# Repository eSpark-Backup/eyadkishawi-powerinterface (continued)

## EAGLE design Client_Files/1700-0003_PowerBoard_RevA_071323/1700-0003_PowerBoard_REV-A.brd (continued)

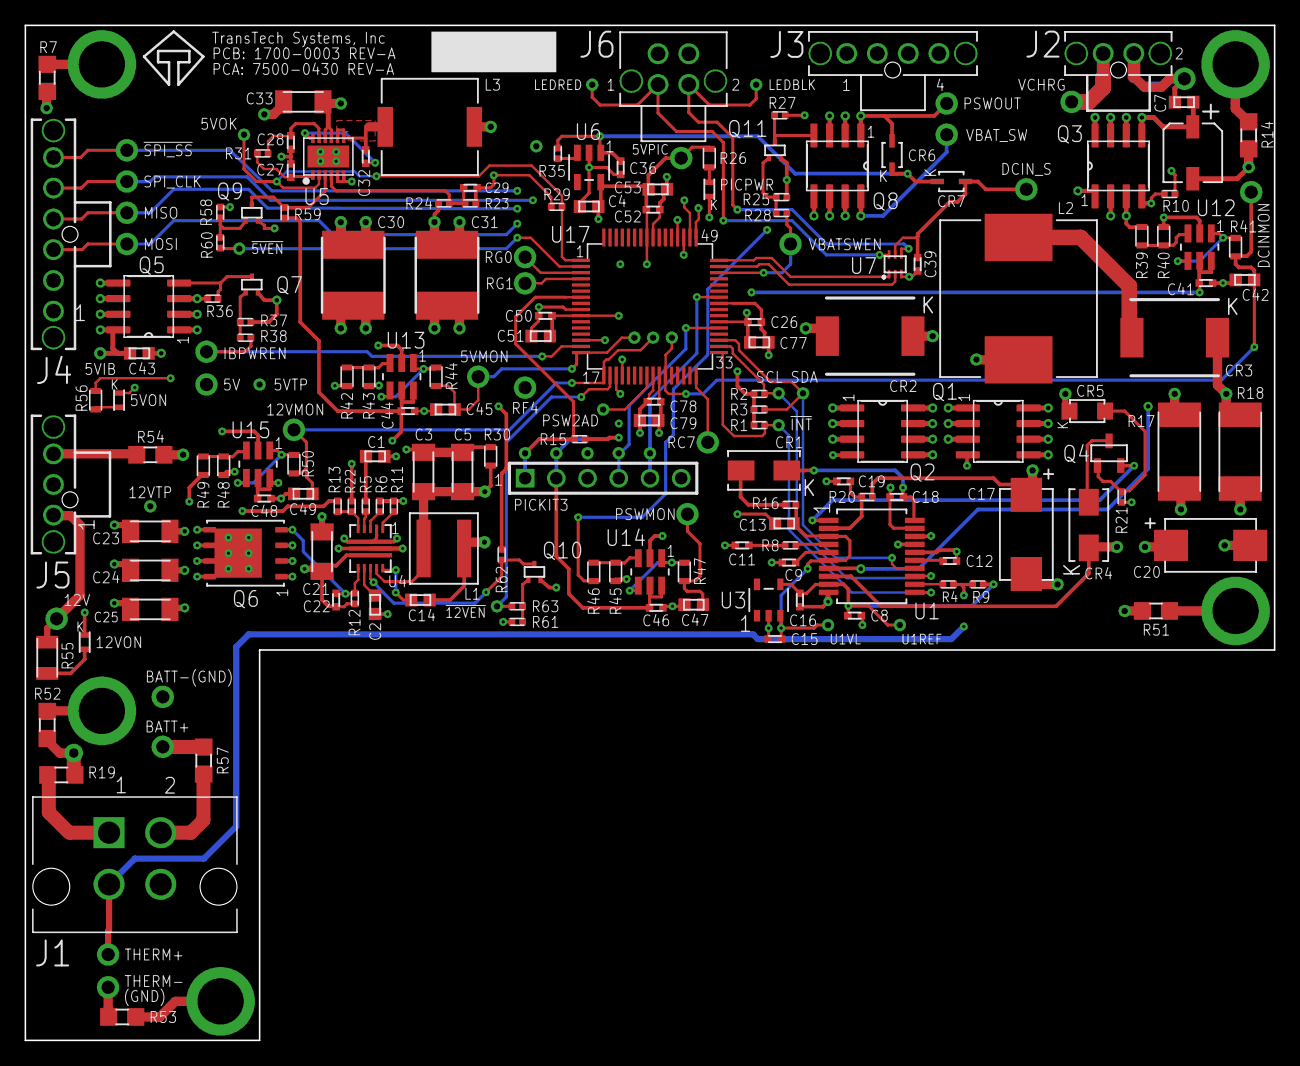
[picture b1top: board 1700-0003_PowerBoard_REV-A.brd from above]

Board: 4 copper layers, 101.6 x 82.5 mm, 205 parts (0 on the bottom side), 100 nets.

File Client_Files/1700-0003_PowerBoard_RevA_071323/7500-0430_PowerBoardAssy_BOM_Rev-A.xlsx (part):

PART | VALUE | DEVICE | PACKAGE | DESCRIPTION | COPYRIGHT | MANUFACTURER | MANUFACTURER_PART_NUMBER | PACKAGE | PART_DESC | QTY_AREA
U4 | REGULATOR_BOOST_TI_TPS61178RNWT | REGULATOR_BOOST_TI_TPS61178RNWT | RNW0013A |  | Copyright (C) 2022 Ultra Librarian. All rights reserved. | TI | TPS61178RNWT |  | IC REG BOOST ADJ 10A 13VQFN
Q1 | N-CH/30V/11A/8-SOIC | MOSFET_N-CH_DIODES-INC_DMS3015SSS-13 | SOIC127P600X175-8N | ENHANCEMENT MODE MOSFET |  | DIODES INC. | DMS3015SSS-13 |  | N-Channel 30 V 11A (Ta) 1.55W (Ta) Surface Mount 8-SO
Q2 | N-CH/30V/11A/8-SOIC | MOSFET_N-CH_DIODES-INC_DMS3015SSS-13 | SOIC127P600X175-8N | ENHANCEMENT MODE MOSFET |  | DIODES INC. | DMS3015SSS-13 |  | N-Channel 30 V 11A (Ta) 1.55W (Ta) Surface Mount 8-SO
C27 | DNP (0402) | CAP_CER_0402_MURATA | G-155_MUR |  |  | MURATA |  |  | --- DO NOT POPULATE ---
U7 | IC_H-BRIDGE_TI_DRV8220DRLR | IC_H-BRIDGE_TI_DRV8220DRLR | SOT5X3-6_DRL_TEX |  |  | TI | DRV8220DRLR |  | 20-V, 1-A H-BRIDGE MOTOR DRIVER
C30 | 47/50V (MLCC-SMD) | CAP_CER_TDK_CKG57 | CAP_CKG57N_TDK |  | Copyright (C) 2022 Ultra Librarian. All rights reserved. | TDK | CKG57NX7R1H476M500JH |  | 47 µF ±20% 50V Ceramic Capacitor X7R Stacked SMD, 2 J-Lead | (2X)
C31 | 47/50V | CAP_CER_TDK_CKG57 | CAP_CKG57N_TDK |  | Copyright (C) 2022 Ultra Librarian. All rights reserved. | TDK | CKG57NX7R1H476M500JH | (SMD-MLCC) | 47 µF ±20% 50V Ceramic Capacitor X7R Stacked SMD, 2 J-Lead | (2X)
Q4 | 45V/0.8A/SOT23 | TRANS_PNP_SOT-23-3_DIOTEC | SOT-23-3_DIOTEC |  |  | DIOTEC | BC807-40 |  | Bipolar Transistors - BJT Bipolar Transistor, SOT-23, 45V, 800mA, PNP
U5 | REGULATOR_BUCK_RENESAS_ISL85005AFRZ-T7A | REGULATOR_BUCK_RENESAS_ISL85005AFRZ-T7A | SON50P300X400X90-13N | RENESAS - ISL85005AFRZ-T7A - DC/DC CONV, SYNC BUCK, DFN-12 |  | RENESAS (INTERSIL) | ISL85005AFRZ-T7A |  | Buck Switching Regulator IC Positive Adjustable 5V 1 Output 5A 12-VFDFN Exposed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
C6 | 45224 | CAP_SMT_EL_CORNELL-DUB_AFK106M25B12T-FCAP_AFK106M25B12T-F_CND-L | CAP_AFK106M25B12T-F_CND-L |  | Copyright (C) 2023 Ultra Librarian. All rights reserved. | Cornell Dubilier | AFK106M25B12T-F |  | CAP ALUM 10UF 20% 25V SMD
C8 | 0.1 (0402) | CAP_CER_0402_MURATA | G-155_MUR |  |  | MURATA | GCM155R71C104KA55D |  | CAP CER 0.1UF 16V X7R 0402
C11 | 0.1 (0402) | CAP_CER_0402_MURATA | G-155_MUR |  |  | MURATA | GCM155R71C104KA55D |  | CAP CER 0.1UF 16V X7R 0402
C15 | 0.1 (0402) | CAP_CER_0402_MURATA | G-155_MUR |  |  | MURATA | GCM155R71C104KA55D |  | CAP CER 0.1UF 16V X7R 0402
C16 | 0.1 (0402) | CAP_CER_0402_MURATA | G-155_MUR |  |  | MURATA | GCM155R71C104KA55D |  | CAP CER 0.1UF 16V X7R 0402
C18 | 0.1 (0402) | CAP_CER_0402_MURATA | G-155_MUR |  |  | MURATA | GCM155R71C104KA55D |  | CAP CER 0.1UF 16V X7R 0402
C19 | 0.1 (0402) | CAP_CER_0402_MURATA | G-155_MUR |  |  | MURATA | GCM155R71C104KA55D |  | CAP CER 0.1UF 16V X7R 0402
C26 | 0.1/16V (0402) | CAP_CER_0402_MURATA | G-155_MUR |  |  | MURATA | GCM155R71C104KA55D |  | CAP CER 0.1UF 16V X7R 0402
C32 | 0.1 (0402) | CAP_CER_0402_MURATA | G-155_MUR |  |  | MURATA | GCM155R71C104KA55D |  | CAP CER 0.1UF 16V X7R 0402
C39 | 0.1 (0402) | CAP_CER_0402_MURATA | G-155_MUR |  |  | MURATA | GCM155R71C104KA55D |  | CAP CER 0.1UF 16V X7R 0402
C41 | 0.1 (0402) | CAP_CER_0402_MURATA | G-155_MUR |  |  | MURATA | GCM155R71C104KA55D |  | CAP CER 0.1UF 16V X7R 0402
C44 | 0.1 (0402) | CAP_CER_0402_MURATA | G-155_MUR |  |  | MURATA | GCM155R71C104KA55D |  | CAP CER 0.1UF 16V X7R 0402
C46 | 0.1 (0402) | CAP_CER_0402_MURATA | G-155_MUR |  |  | MURATA | GCM155R71C104KA55D |  | CAP CER 0.1UF 16V X7R 0402
C48 | 0.1 (0402) | CAP_CER_0402_MURATA | G-155_MUR |  |  | MURATA | GCM155R71C104KA55D |  | CAP CER 0.1UF 16V X7R 0402
C50 | 0.1/16V (0402) | CAP_CER_0402_MURATA | G-155_MUR |  |  | MURATA | GCM155R71C104KA55D |  | CAP CER 0.1UF 16V X7R 0402
C52 | 0.1/16V (0402) | CAP_CER_0402_MURATA | G-155_MUR |  |  | MURATA | GCM155R71C104KA55D |  | CAP CER 0.1UF 16V X7R 0402
C78 | 0.1/16V (0402) | CAP_CER_0402_MURATA | G-155_MUR |  |  | MURATA | GCM155R71C104KA55D |  | CAP CER 0.1UF 16V X7R 0402
C42 | 0.1/25V (0603) | CAP_CER_0603_TDK | CAP_C1608_TDK |  |  | KEMET | C0603C104K3RAC7867 |  | CAP CER 0.1UF 25V X7R 0603
C45 | 0.1/25V (0603) | CAP_CER_0603_TDK | CAP_C1608_TDK |  |  | KEMET | C0603C104K3RAC7867 |  | CAP CER 0.1UF 25V X7R 0603
C47 | 0.1/25V (0603) | CAP_CER_0603_TDK | CAP_C1608_TDK |  |  | KEMET | C0603C104K3RAC7867 |  | CAP CER 0.1UF 25V X7R 0603
C49 | 0.1/25V (0603) | CAP_CER_0603_TDK | CAP_C1608_TDK |  |  | KEMET | C0603C104K3RAC7867 |  | CAP CER 0.1UF 25V X7R 0603
C7 | 0.1/50V | CAP_CER_0603_TDK | CAP_C1608_TDK |  |  | SAMSUNG | CL10B104KB8NNNC | -603 | CAP CER 0.1UF 50V X7R 0603
C14 | 0.1/50V | CAP_CER_0603_TDK | CAP_C1608_TDK |  |  | SAMSUNG | CL10B104KB8NNNC | -603 | CAP CER 0.1UF 50V X7R 0603
C12 | 22nF (0402) | CAP_CER_0402_MURATA | G-155_MUR |  |  | MURATA | C0402C223K5REC7411 |  | CAP CER 0402 22NF 50V X7R 10%
C9 | 47nF (0402) | CAP_CER_0402_MURATA | G-155_MUR |  |  | MURATA | C0402C473K3REC7867 |  | CAP CER 0402 47NF 25V X7R 10%
C43 | 10/10V (0603) | CAP_CER_0603_TDK | CAP_C1608_TDK |  |  | MURATA | GRM188D71A106KA73D |  | CAP CER 10UF 10V X7T 0603
C51 | 10/10V (0603) | CAP_CER_0603_TDK | CAP_C1608_TDK |  |  | MURATA | GRM188D71A106KA73D |  | CAP CER 10UF 10V X7T 0603
C53 | 10/10V (0603) | CAP_CER_0603_TDK | CAP_C1608_TDK |  |  | MURATA | GRM188D71A106KA73D |  | CAP CER 10UF 10V X7T 0603
C77 | 10/10V (0603) | CAP_CER_0603_TDK | CAP_C1608_TDK |  |  | MURATA | GRM188D71A106KA73D |  | CAP CER 10UF 10V X7T 0603
C79 | 10/10V (0603) | CAP_CER_0603_TDK | CAP_C1608_TDK |  |  | MURATA | GRM188D71A106KA73D |  | CAP CER 10UF 10V X7T 0603
C21 | 10/50V (1206) | CAP_CER_1206_SAMSUNG | CAP_CL31_SAM |  | Copyright (C) 2022 Ultra Librarian. All rights reserved. | SAMSUNG | CL31B106KBHNNNE |  | CAP CER 10UF 50V X7R 1206 | (__X)
C29 | 12pF (0402) | CAP_CER_0402_MURATA | G-155_MUR |  |  | MURATA | C0402C120K5RAC7867 |  | CAP CER 12PF 50V X7R 0402
C28 | 1/25V (0402) | CAP_CER_0402_MURATA | G-155_MUR |  |  | MURATA | GRM155R61E105KA12D |  | CAP CER 1UF 25V X5R 0402
C13 | 1/25V | CAP_CER_0603_TDK | CAP_C1608_TDK |  |  | SAMSUNG | CL10B105KA8NNNC | -603 | CAP CER 1UF 25V X7R 0603
C36 | 1/10V (0402) | CAP_CER_0402_MURATA | G-155_MUR |  |  | MURATA | GRM155C81C225ME15D |  | CAP CER 2.2UF 16V X6S 0402
C1 | 220pF (0603) | CAP_CER_0603_TDK | CAP_C1608_TDK |  |  | SAMSUNG | CL10C221JB8NNNC |  | CAP CER 220PF 50V C0G/NP0 0603
C3 | 22/25V (1206) | CAP_CER_1206_SAMSUNG | CAP_CL31_SAM |  | Copyright (C) 2022 Ultra Librarian. All rights reserved. | SAMSUNG | CL31A226KAHNNNE |  | CAP CER 22UF 25V X5R 1206
C5 | 22/25V (1206) | CAP_CER_1206_SAMSUNG | CAP_CL31_SAM |  | Copyright (C) 2022 Ultra Librarian. All rights reserved. | SAMSUNG | CL31A226KAHNNNE |  | CAP CER 22UF 25V X5R 1206 | (2X)
C33 | 22/25V (1206) | CAP_CER_1206_SAMSUNG | CAP_CL31_SAM |  | Copyright (C) 2022 Ultra Librarian. All rights reserved. | SAMSUNG | CL31A226KAHNNNE |  | CAP CER 22UF 25V X5R 1206 | (2X)
C23 | 22/25V (1206) | CAP_CER_1206_SAMSUNG | CAP_CL31_SAM |  | Copyright (C) 2022 Ultra Librarian. All rights reserved. | SAMSUNG | GCM31CC81E226KE11L |  | CAP CER 22UF 25V X6S 1206 | (3X)
C24 | 22/25V (1206) | CAP_CER_1206_SAMSUNG | CAP_CL31_SAM |  | Copyright (C) 2022 Ultra Librarian. All rights reserved. | SAMSUNG | GCM31CC81E226KE11L |  | CAP CER 22UF 25V X6S 1206 | (3X)
C25 | 22/25V (1206) | CAP_CER_1206_SAMSUNG | CAP_CL31_SAM |  | Copyright (C) 2022 Ultra Librarian. All rights reserved. | SAMSUNG | GCM31CC81E226KE11L |  | CAP CER 22UF 25V X6S 1206 | (3X)
C2 | 4.7/16V (0603) | CAP_CER_0603_TDK | CAP_C1608_TDK |  |  | MURATA | GRM188Z71C475KE21D |  | CAP CER 4.7UF 16V X7R 0603
C4 | 4.7/16V (0603) | CAP_CER_0603_TDK | CAP_C1608_TDK |  |  | MURATA | GRM188Z71C475KE21D |  | CAP CER 4.7UF 16V X7R 0603
C17 | 22/35 (2917) | CAP_TANT_KEMET_2917 | CAPMP7.6X4.3_3.1N_KEM |  | Copyright (C) 2022 Ultra Librarian. All rights reserved. | KEMET | T495D226K035ATE300 |  | CAP TANT 22UF 10% 35V 2917
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
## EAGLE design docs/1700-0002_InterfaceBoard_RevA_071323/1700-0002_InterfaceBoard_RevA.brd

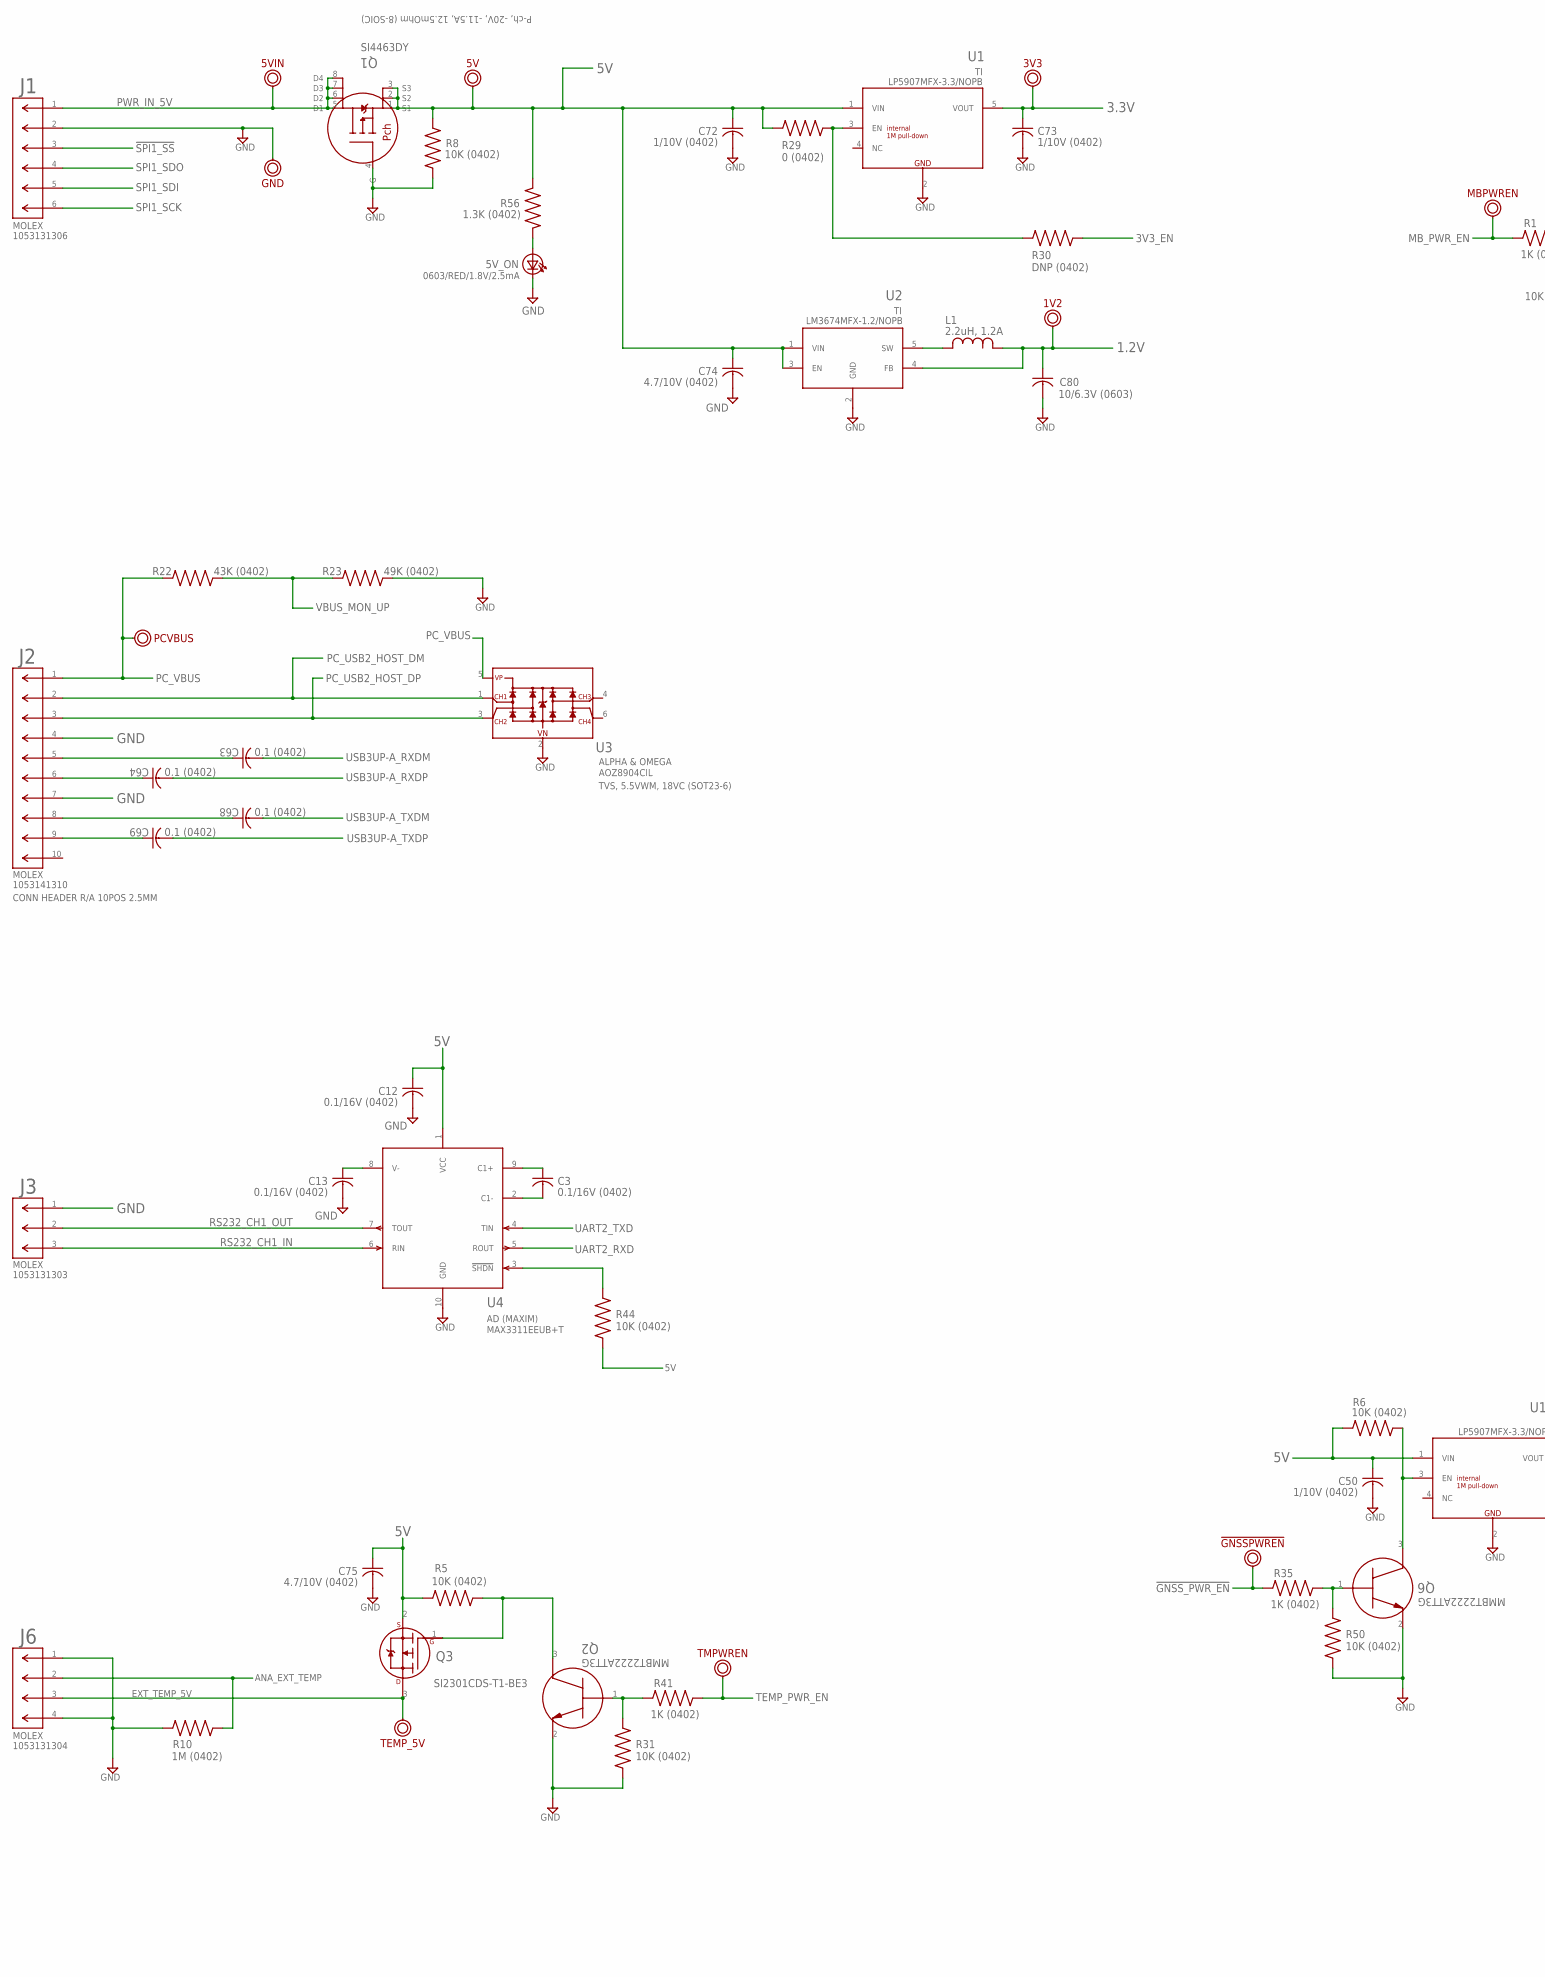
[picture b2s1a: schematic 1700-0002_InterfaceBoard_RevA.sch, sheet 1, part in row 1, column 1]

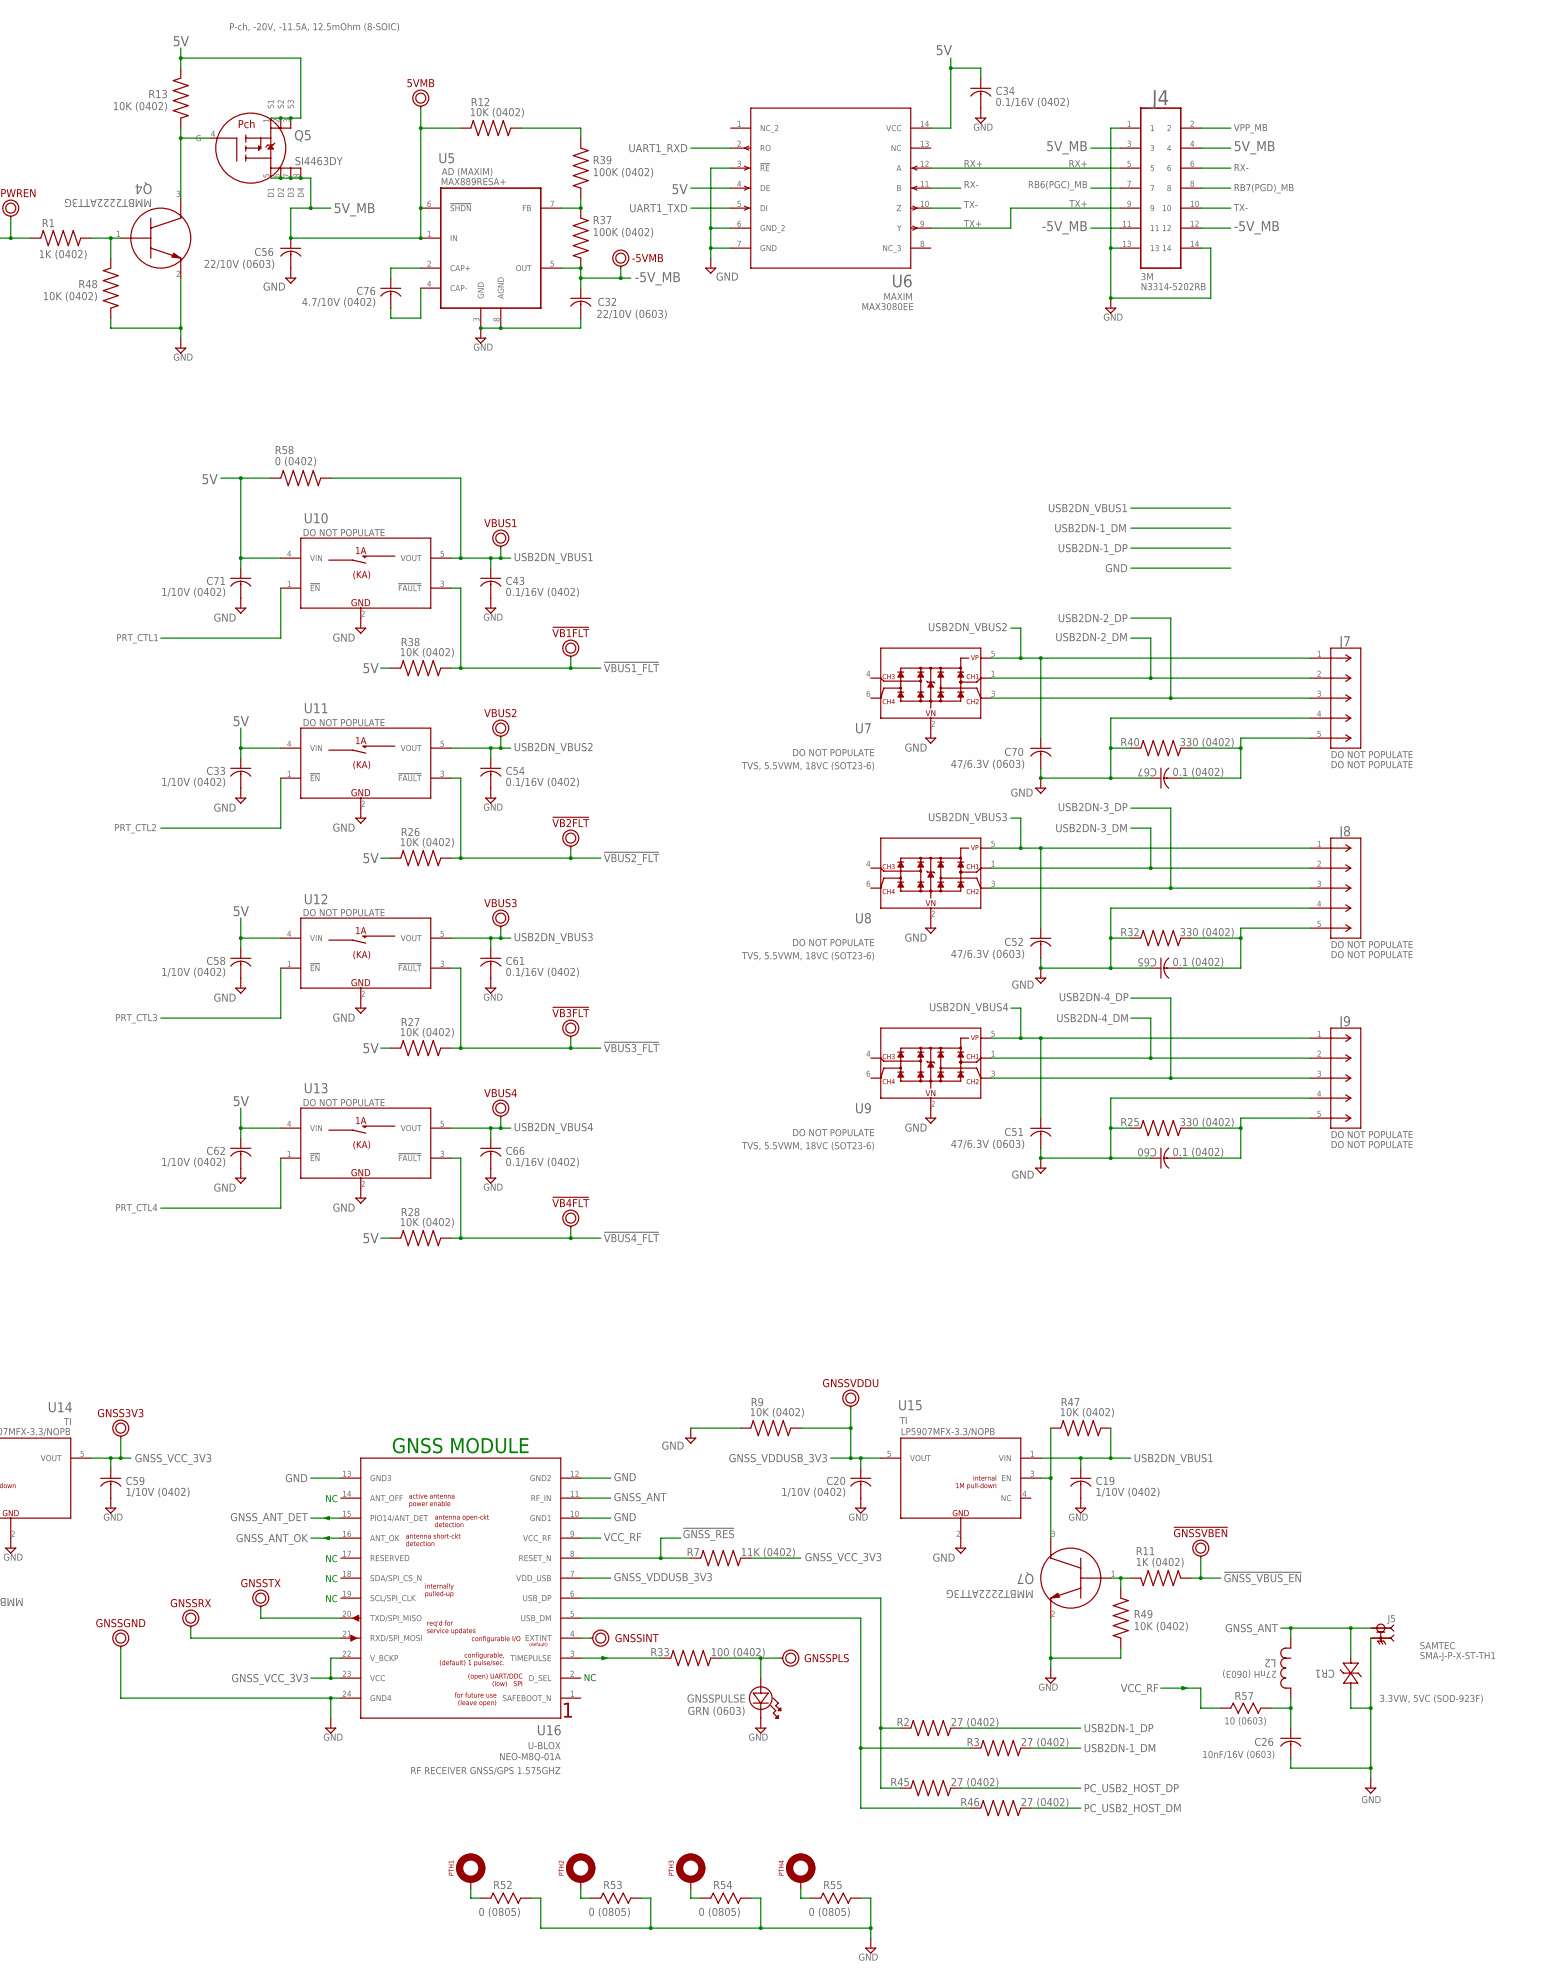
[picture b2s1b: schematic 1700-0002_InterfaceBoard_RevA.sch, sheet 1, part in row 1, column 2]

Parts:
1V2, 3V3, 5V, 5VIN, 5VMB: TST_POINT_PTH_042-OCT
5V_ON: 0603/RED/1.8V/2.5mA; LED_0603_LITE-ON
!GNSSPWREN: TST_POINT_PTH_042-OCT
!GNSSVBEN: TST_POINT_PTH_042-OCT
!VB1FLT, !VB2FLT, !VB3FLT, !VB4FLT: TST_POINT_PTH_042-OCT
-5VMB: TST_POINT_PTH_042-OCT
C3, C12, C13, C34: 0.1/16V (0402); G-155_MUR
C19, C20, C50, C59, C72, C73: 1/10V (0402); G-155_MUR; MANUFACTURER_PART_NUMBER GCM155C71A105KE38D
C26: 10nF/16V (0603); CAP_C1608_TDK; MANUFACTURER_PART_NUMBER C0603C103K4REC7867
C32, C56: 22/10V (0603); CAP_C1608_TDK; MANUFACTURER_PART_NUMBER GRM188R61A226ME15D
C33, C58, C62, C71: 1/10V (0402); G-155_MUR; MANUFACTURER_PART_NUMBER DO NOT POPULATE
C43, C54, C61, C66: 0.1/16V (0402); G-155_MUR; MANUFACTURER_PART_NUMBER DO NOT POPULATE
C51, C52, C70: 47/6.3V (0603); CAP_C1608_TDK; MANUFACTURER_PART_NUMBER DO NOT POPULATE
C60, C65, C67: 0.1 (0402); G-155_MUR; MANUFACTURER_PART_NUMBER DO NOT POPULATE
C63, C64, C68, C69: 0.1 (0402); G-155_MUR
C74, C75, C76: 4.7/10V (0402); G-155_MUR; MANUFACTURER_PART_NUMBER C1005X5R1A475K050BE
C80: 10/6.3V (0603); CAP_C1608_TDK; MANUFACTURER_PART_NUMBER C0805X106M9RAC7800
CR1: 3.3VW, 5VC (SOD-923F); SOD-923F_COMCHIP
GND: TST_POINT_PTH_042-OCT
GNSS3V3: TST_POINT_PTH_042-OCT
GNSSGND: TST_POINT_PTH_042-OCT
GNSSINT: TST_POINT_PTH_042-OCT
GNSSPLS: TST_POINT_PTH_042-OCT
GNSSPULSE: GRN (0603); LED_DIALIGHT_598_DIA
GNSSRX: TST_POINT_PTH_042-OCT
GNSSTX: TST_POINT_PTH_042-OCT
GNSSVDDU: TST_POINT_PTH_042-OCT
J1: CON_MOLEX_1053131306; CON_1053131306
J2: CON_MOLEX_1053141310; CON_1053141310
J3: CON_MOLEX_1053131303; CON_1053131303
J4: CON_3M_RA_N3314-5302RB; 3M_N3314-5302RB_RA; MANUFACTURER_PART_NUMBER N3314-5202RB
J5: SAMTEC_SMA-J-P-X-ST-TH1_V.2; SAMTEC_SMA-J-P-X-ST-TH1
J6: CON_MOLEX_1053131304; CON_1053131304
J7, J8, J9: CON_MOLEX_1054301305; CON_1054301305_MOL; MANUFACTURER_PART_NUMBER DO NOT POPULATE
L1: 2.2uH, 1.2A; IND_TAIYO_NR3012_TAY
L2: 27nH (0603); INDUCTOR_0603_TDK
MBPWREN: TST_POINT_PTH_042-OCT
PCVBUS: TST_POINT_PTH_042-OCT
PTH1, PTH2, PTH3, PTH4: PTH_M4_4.5MM-ID_MIDDLE-FIT; PTH_M4_4.5MM-ID; PART_DESC PCB feature, PTH mounting (hole), M4
Q1, Q5: P-ch, -20V, -11.5A, 12.5mOhm (8-SOIC); SO-8L-NB_FAS; MANUFACTURER_PART_NUMBER SI4463DY
Q2, Q4, Q6, Q7: MMBT2222ATT3G; SC-75(SOT-416)_ONSEMI
Q3: P-CH/-20V/-3A/0.09OHM; SOT_1CDS-T1-BE3_VIS
R1, R11, R35, R41: 1K (0402); RESC1005X35N; MANUFACTURER_PART_NUMBER CRCW04021K00FKEDC
R2, R3: 27 (0402); RESC1005X35N; MANUFACTURER_PART_NUMBER DO NOT POPULATE
R5, R6, R8, R9, R12, R13, R31, R44, R47, R48, R49, R50: 10K (0402); RESC1005X35N
R7: 11K (0402); RESC1005X35N; MANUFACTURER_PART_NUMBER RMCF0402FT11K0
R10: 1M (0402); RESC1005X35N; MANUFACTURER_PART_NUMBER CRGCQ0402F1M0
R22: 43K (0402); RESC1005X35N; MANUFACTURER_PART_NUMBER RCS040243K0FKED
R23: 49K (0402); RESC1005X35N; MANUFACTURER_PART_NUMBER CRCW040249K9FKEDC
R25, R32, R40: 330 (0402); RESC1005X35N; MANUFACTURER_PART_NUMBER DO NOT POPULATE
R26, R27, R28, R38: 10K (0402); RESC1005X35N; MANUFACTURER_PART_NUMBER DO NOT POPULATE
R29, R58: 0 (0402); RESC1005X35N; MANUFACTURER_PART_NUMBER CRCW04020000Z0EDC
R30: DNP (0402); RESC1005X35N; MANUFACTURER_PART_NUMBER CRCW04020000Z0EDC
R33: 100 (0402); RESC1005X35N; MANUFACTURER_PART_NUMBER CRCW0402100RFKEDC
R37, R39: 100K (0402); RESC1005X35N; MANUFACTURER_PART_NUMBER CRCW0402100KFKEDC
R45, R46: 27 (0402); RESC1005X35N; MANUFACTURER_PART_NUMBER CRGCQ0402F27R
R52, R53, R54, R55: 0 (0805); STA_HCJ0805_STP
R56: 1.3K (0402); RESC1005X35N; MANUFACTURER_PART_NUMBER CRCW04021K30FKED
R57: 10 (0603); STA_RMCF0603_STP; MANUFACTURER_PART_NUMBER TNPW060310R0FHTA
TEMP_5V: TST_POINT_PTH_042-OCT
TMPWREN: TST_POINT_PTH_042-OCT
U1, U14, U15: TI_LP5907MFX-3.3/NOPBDBV0005A_L; DBV0005A_L
U2: TI_SW-REG_LM3671; DBV5_TEX; MANUFACTURER_PART_NUMBER LM3674MFX-1.2/NOPB
U3: TVS, 5.5VWM, 18VC (SOT23-6); SOT-23-6_AOS; PART_DESC TVS DIODE 5.5VWM 18VC SOT23-6
U4: MAXIM_MAX3311EEUB+T; 21-0061L_MXM; MANUFACTURER_PART_NUMBER MAX3311EEUB+T
U5: MAXIM_MAX889RESA; SOIC127P600X175-8N; PART_DESC Charge Pump Switching Regulator IC Nega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
U6: MAX3080EESD+; 21-0041B_14_MXM; MANUFACTURER_PART_NUMBER MAX3080EE
U7, U8, U9: TVS, 5.5VWM, 18VC (SOT23-6); SOT-23-6_AOS; MANUFACTURER_PART_NUMBER DO NOT POPULATE
U10, U11, U12, U13: SW_PWR_1CH_DIODES-INC_AP22816BKAWT; TSOT-25_DIODES-INC; MANUFACTURER_PART_NUMBER DO NOT POPULATE
U16: MODULE_UBLOX_NEO-M8Q-01A; UBLOX_24LCC
VBUS1, VBUS2, VBUS3, VBUS4: TST_POINT_PTH_042-OCT

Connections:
1.2V: 1V2.P$1, C80.1, L1.1, U2.4 (FB); also elsewhere on the board
3.3V: 3V3.P$1, C73.1, U1.5 (VOUT); also elsewhere on the board
3V3_EN: R30.2; also elsewhere on the board
5V: 5V.P$1, C12.1, C33.1, C34.1, C50.1, C58.1, C62.1, C71.1, C72.1, C74.1, C75.1, Q1.1 (S1), Q1.2 (S2), Q1.3 (S3), Q3.2 (S), Q5.1 (S1), Q5.2 (S2), Q5.3 (S3), R5.2, R6.2, R8.2, R13.1, R26.2, R27.2, R28.2, R29.1, R38.2, R44.2, R56.2, R58.1, U1.1 (VIN), U2.1 (VIN), U2.3 (EN), U4.1 (VCC), U6.4 (DE), U6.14 (VCC), U10.4 (VIN), U11.4 (VIN), U12.4 (VIN), U13.4 (VIN), U14.1 (VIN); also elsewhere on the board
5V_MB: 5VMB.P$1, C56.1, J4.3, J4.4, Q5.5 (D1), Q5.6 (D2), Q5.7 (D3), Q5.8 (D4), R12.2, U5.1 (IN), U5.6 (!SHDN); also elsewhere on the board
!GNSS_PWR_EN: !GNSSPWREN.P$1, R35.1; also elsewhere on the board
!GNSS_RES: R7.1, U16.8 (RESET_N); also elsewhere on the board
!GNSS_VBUS_EN: !GNSSVBEN.P$1, R11.1; also elsewhere on the board
!SPI1_SS: J1.3; also elsewhere on the board
!VBUS1_FLT: !VB1FLT.P$1, R38.1, U10.3 (!FAULT); also elsewhere on the board
!VBUS2_FLT: !VB2FLT.P$1, R26.1, U11.3 (!FAULT); also elsewhere on the board
!VBUS3_FLT: !VB3FLT.P$1, R27.1, U12.3 (!FAULT); also elsewhere on the board
!VBUS4_FLT: !VB4FLT.P$1, R28.1, U13.3 (!FAULT); also elsewhere on the board
-5V_MB: -5VMB.P$1, C32.1, J4.11, J4.12, R37.2, U5.5 (OUT)
ANA_EXT_TEMP: J6.2, R10.1; also elsewhere on the board
EXT_TEMP_5V: J6.3, Q3.3 (D), TEMP_5V.P$1
GND: 5V_ON.1 (K2), C12.2, C13.2, C19.2, C20.2, C26.2, C32.2, C33.2, C34.2, C43.2, C50.2, C51.2, C52.2, C54.2, C56.2, C58.2, C59.2, C60.1, C61.2, C62.2, C65.1, C66.2, C67.1, C70.2, C71.2, C72.2, C73.2, C74.2, C75.2, C80.2, CR1.2 (K), GND.P$1, GNSSGND.P$1, GNSSPULSE.1, J1.2, J2.4, J2.7, J3.1, J4.1, J4.13, J4.14, J5.2, J5.3 (2), J5.4 (2), J5.5 (2), J6.1, J6.4, J7.4, J8.4, J9.4, Q1.4 (G), Q2.2 (E), Q4.2 (E), Q6.2 (E), Q7.2 (E), R8.1, R9.2, R10.2, R23.1, R25.2, R31.2, R32.2, R40.2, R48.2, R49.2, R50.2, R52.1, R53.1, R54.1, R55.1, U1.2 (GND), U2.2 (GND), U3.2 (VN), U4.10 (GND), U5.3 (GND), U5.8 (AGND), U6.3 (!RE), U6.6 (GND_2), U6.7 (GND), U7.2 (VN), U8.2 (VN), U9.2 (VN), U10.2 (GND), U11.2 (GND), U12.2 (GND), U13.2 (GND), U14.2 (GND), U15.2 (GND), U16.10 (GND1), U16.12 (GND2), U16.13 (GND3), U16.24 (GND4); also elsewhere on the board
GNSS_ANT: CR1.1 (A), J5.1, L2.1, U16.11 (RF_IN)
GNSS_ANT_DET: U16.15 (PIO14/ANT_DET); also elsewhere on the board
GNSS_ANT_OK: U16.16 (ANT_OK); also elsewhere on the board
GNSS_VCC_3V3: C59.1, GNSS3V3.P$1, R7.2, U14.5 (VOUT), U16.22 (V_BCKP), U16.23 (VCC)
GNSS_VDDUSB_3V3: C20.1, GNSSVDDU.P$1, R9.1, U15.5 (VOUT), U16.7 (VDD_USB)
MB_PWR_EN: MBPWREN.P$1, R1.1; also elsewhere on the board
unnamed: L1.2, U2.5 (SW)
unnamed: C3.1, U4.9 (C1+)
unnamed: PTH1.P$1, R52.2
unnamed: C3.2, U4.2 (C1-)
unnamed: C13.1, U4.8 (V-)
unnamed: R29.2, R30.1, U1.3 (EN)
unnamed: PTH2.P$1, R53.2
unnamed: Q2.3 (C), Q3.1 (G), R5.1
unnamed: Q2.1 (B), R31.1, R41.1
unnamed: R2.1, R45.1, U16.6 (USB_DP)
unnamed: R3.1, R46.1, U16.5 (USB_DM)
unnamed: Q6.3 (C), R6.1, U14.3 (EN)
unnamed: GNSSTX.P$1, U16.20 (TXD/SPI_MISO)
unnamed: PTH3.P$1, R54.2
unnamed: Q6.1 (B), R35.2, R50.1
unnamed: Q7.3 (C), R47.2, U15.3 (EN)
unnamed: C60.2, J9.5, R25.1
unnamed: PTH4.P$1, R55.2
unnamed: Q4.3 (C), Q5.4 (G), R13.2
unnamed: C65.2, J8.5, R32.1
unnamed: R37.1, R39.2, U5.7 (FB)
unnamed: C69.1, J2.9
unnamed: C68.1, J2.8
unnamed: C64.1, J2.6
unnamed: C63.1, J2.5
unnamed: Q4.1 (B), R1.2, R48.1
unnamed: GNSSRX.P$1, U16.21 (RXD/SPI_MOSI)
unnamed: R33.1, U16.3 (TIMEPULSE)
unnamed: GNSSINT.P$1, U16.4 (EXTINT)
unnamed: R12.1, R39.1
unnamed: C76.1, U5.2 (CAP+)
unnamed: C76.2, U5.4 (CAP-)
unnamed: 5V_ON.2 (A2), R56.1
unnamed: GNSSPLS.P$1, GNSSPULSE.2, R33.2
unnamed: C67.2, J7.5, R40.1
unnamed: R44.1, U4.3 (!SHDN)
unnamed: C26.1, L2.2, R57.1
PC_USB2_HOST_DM: J2.2, R46.2, U3.1 (CH1); also elsewhere on the board
PC_USB2_HOST_DP: J2.3, R45.2, U3.3 (CH2); also elsewhere on the board
PC_VBUS: J2.1, PCVBUS.P$1, R22.2, U3.5 (VP)
PRT_CTL1: U10.1 (!EN); also elsewhere on the board
PRT_CTL2: U11.1 (!EN); also elsewhere on the board
PRT_CTL3: U12.1 (!EN); also elsewhere on the board
PRT_CTL4: U13.1 (!EN); also elsewhere on the board
PWR_BYP2: Q7.1 (B), R11.2, R49.1
PWR_IN_5V: 5VIN.P$1, J1.1, Q1.5 (D1), Q1.6 (D2), Q1.7 (D3), Q1.8 (D4)
RB6(PGC)_MB: J4.7; also elsewhere on the board
RB7(PGD)_MB: J4.8; also elsewhere on the board
RS232_CH1_IN: J3.3, U4.6 (RIN)
RS232_CH1_OUT: J3.2, U4.7 (TOUT)
RX+: J4.5, U6.12 (A)
RX-: J4.6, U6.11 (B)
SPI1_SCK: J1.6; also elsewhere on the board
SPI1_SDI: J1.5; also elsewhere on the board
SPI1_SDO: J1.4; also elsewhere on the board
TEMP_PWR_EN: R41.2, TMPWREN.P$1; also elsewhere on the board
TX+: J4.9, U6.9 (Y)
TX-: J4.10, U6.10 (Z)
UART1_RXD: U6.2 (RO); also elsewhere on the board
UART1_TXD: U6.5 (DI); also elsewhere on the board
UART2_RXD: U4.5 (ROUT); also elsewhere on the board
UART2_TXD: U4.4 (TIN); also elsewhere on the board
USB2DN-1_DM: R3.2; also elsewhere on the board
USB2DN-1_DP: R2.2; also elsewhere on the board
USB2DN-2_DM: J7.2, U7.1 (CH1); also elsewhere on the board
USB2DN-2_DP: J7.3, U7.3 (CH2); also elsewhere on the board
USB2DN-3_DM: J8.2, U8.1 (CH1); also elsewhere on the board
USB2DN-3_DP: J8.3, U8.3 (CH2); also elsewhere on the board
USB2DN-4_DM: J9.2, U9.1 (CH1); also elsewhere on the board
USB2DN-4_DP: J9.3, U9.3 (CH2); also elsewhere on the board
USB2DN_VBUS1: C19.1, C43.1, R47.1, R58.2, U10.5 (VOUT), U15.1 (VIN), VBUS1.P$1
USB2DN_VBUS2: C54.1, C70.1, J7.1, U7.5 (VP), U11.5 (VOUT), VBUS2.P$1
USB2DN_VBUS3: C52.1, C61.1, J8.1, U8.5 (VP), U12.5 (VOUT), VBUS3.P$1
USB2DN_VBUS4: C51.1, C66.1, J9.1, U9.5 (VP), U13.5 (VOUT), VBUS4.P$1
USB3UP-A_RXDM: C63.2; also elsewhere on the board
USB3UP-A_RXDP: C64.2; also elsewhere on the board
USB3UP-A_TXDM: C68.2; also elsewhere on the board
USB3UP-A_TXDP: C69.2; also elsewhere on the board
VBUS_MON_UP: R22.1, R23.2; also elsewhere on the board
VCC_RF: R57.2, U16.9 (VCC_RF)
VPP_MB: J4.2; also elsewhere on the board

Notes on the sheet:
GNSS MODULE
